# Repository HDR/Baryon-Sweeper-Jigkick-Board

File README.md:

# Baryon-Sweeper-Jigkick-Board
Small cheap JigKick pcb for unbricking the PSP-3000 (Untested)

Designed for use with PL2303HX RS232 TTL adapters (Not PL2303, unless you use jumper wires)

Purchase on [OshPark](https://oshpark.com/shared_projects/5V3BZEFr)

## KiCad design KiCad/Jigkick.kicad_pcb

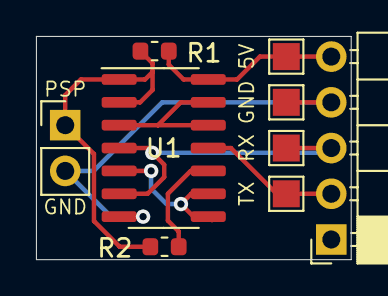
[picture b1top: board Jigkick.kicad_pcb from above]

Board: 2 copper layers, 17.5 x 12.4 mm, 9 parts (0 on the bottom side), 8 nets.

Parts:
5V: 5V; TestPoint_Pad_1.5x1.5mm
GND: GND; TestPoint_Pad_1.5x1.5mm
J1: TTL Header; PinSocket_1x05_P2.54mm_Horizontal
J2: PSP; PinHeader_1x02_P2.54mm_Vertical
R1: 10K; R_0603_1608Metric
R2: 330; R_0603_1608Metric
RX: RX; TestPoint_Pad_1.5x1.5mm
TX: TX; TestPoint_Pad_1.5x1.5mm
U1: SN74AHCT00DR; SOIC-14_3.9x8.7mm_P1.27mm

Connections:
1: J2.1, R1.1, R2.1, U1.1, U1.2
2B: U1.5, U1.8, U1.9
3R: R2.2, U1.10
5V: 5V.1, J1.5, R1.2, U1.14
GND: GND.1, J1.4, J2.2, U1.7
RX: J1.3, RX.1, U1.4, U1.6
TX: J1.2, TX.1, U1.11
Y1: U1.3, U1.12, U1.13

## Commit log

2021-01-12 add pdf
